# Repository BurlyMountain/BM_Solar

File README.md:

# BM_Solar 

This little PCB uses a Texas Instruments bq25185 chip to act as a solar charge controller and battery managment system for single cell Lithium Polymer, Lithium Ion, or Lithium Phosphate batteries.

It was designed specifically to work as a hat for Waveshare RP2040-LoRa boards to improve charging and battery managment as a solar meshtastic router/repeater. It is the same footprint and will solder directly on the backside of a RP2040-LoRa board.

*(Though it was designed for the RP2040-LoRa, it will work with any other board that can run off of a 4.5V input.)*

# Specifications

- 1A max charge rate (limited by solar input)
- Stable 4.5V output to a device
- 3-18V solar input voltage
- Automatically switches to battery power once solar drops below 3V
- Uses a 10kOhm thermistor to stop charging below 0F/32C in order to prevent damage to the battery
- Much more efficient than built in solar charging on most Meshtastic boards with near MPPT efficiency
- Selectable charge profile between LiPo/LiIon and LFP with an easy jumper
- built in voltage divider for battery voltage monitoring

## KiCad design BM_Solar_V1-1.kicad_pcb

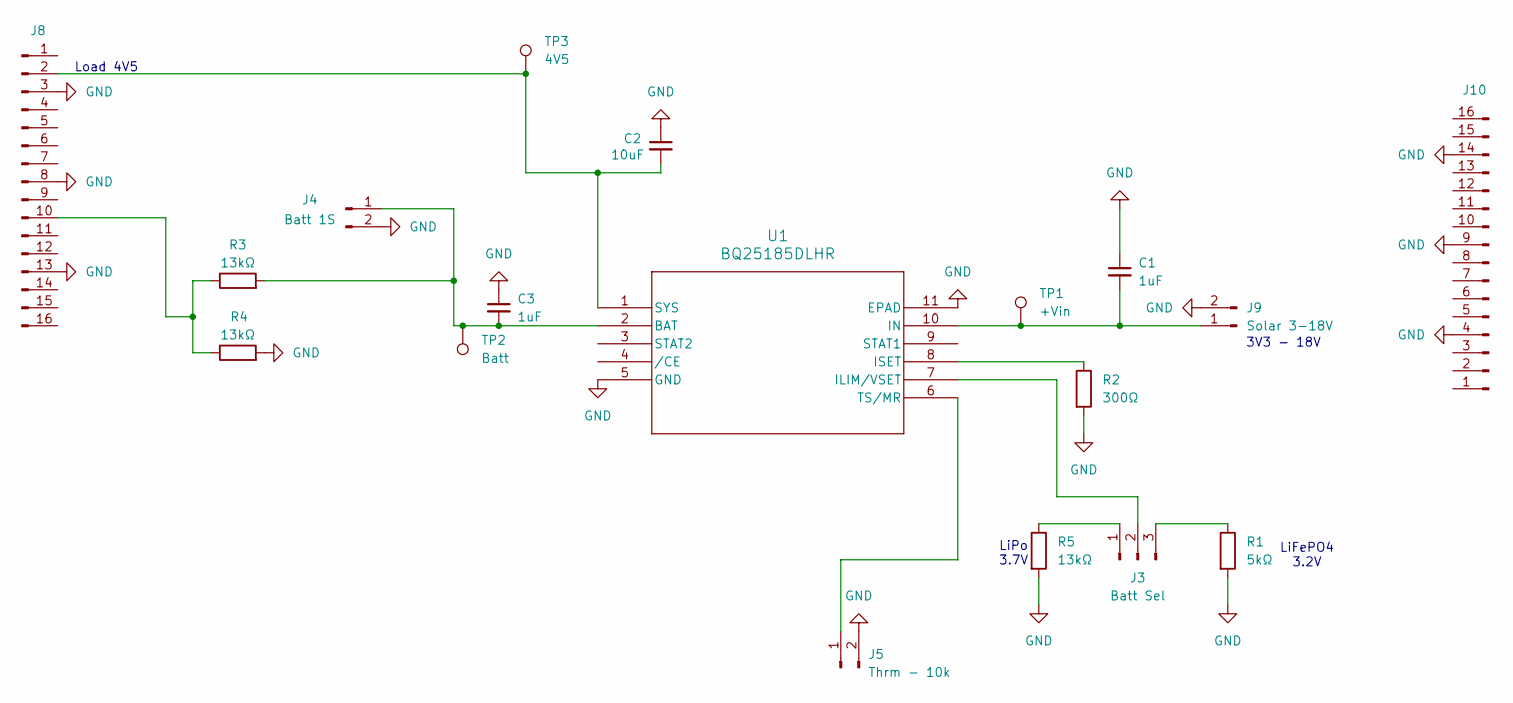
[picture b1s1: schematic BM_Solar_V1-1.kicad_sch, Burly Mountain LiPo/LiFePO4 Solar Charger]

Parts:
C1, C3: 1uF; C_0805_2012Metric
C2: 10uF; C_0805_2012Metric
J3: Batt Sel; PinHeader_1x03_P2.54mm_Vertical
J4: Batt 1S; JST_PH_S2B-PH-K_1x02_P2.00mm_Horizontal
J5: Thrm - 10k; SolderWire-0.5sqmm_1x02_P4.6mm_D0.9mm_OD2.1mm
J8, J10: Conn_01x16_Pin; PinHeader_1x16_P2.54mm_Vertical
J9: Solar 3-18V; JST_PH_S2B-PH-K_1x02_P2.00mm_Horizontal
R1: 5kΩ; R_0805_2012Metric
R2: 300Ω; R_0805_2012Metric
R3, R4, R5: 13kΩ; R_0805_2012Metric
TP1: +Vin; TestPoint_Pad_D1.0mm
TP2: Batt; TestPoint_Pad_D1.0mm
TP3: 4V5; TestPoint_Pad_D1.0mm
U1: BQ25185DLHR; WSON10_DLH_TEX

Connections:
GND: C1.1, C2.1, C3.1, J4.2, J5.2, J8.3, J8.8, J8.13, J9.2, J10.4, J10.9, J10.14, R1.2, R2.2, R4.2, R5.2, U1.5 (GND), U1.11 (EPAD)
unnamed: J3.1, R5.1
unnamed: J3.2, U1.7 (ILIM/VSET)
unnamed: J3.3, R1.1
unnamed: C3.2, J4.1, R3.2, TP2.1, U1.2 (BAT)
unnamed: J5.1, U1.6 (TS/MR)
unnamed: C2.2, J8.2, TP3.1, U1.1 (SYS)
unnamed: J8.10, R3.1, R4.1
unnamed: C1.2, J9.1, TP1.1, U1.10 (IN)
unnamed: R2.1, U1.8 (ISET)

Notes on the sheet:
Load 4V5
3V3 - 18V
LiFePO4 3.2V
LiPo 3.7V

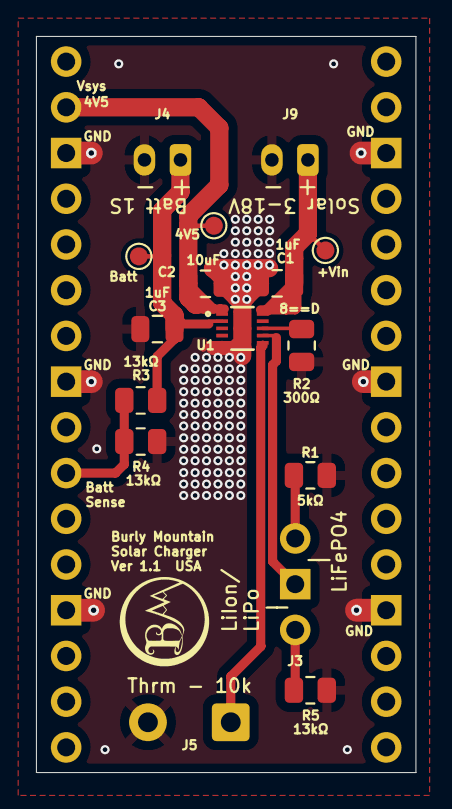
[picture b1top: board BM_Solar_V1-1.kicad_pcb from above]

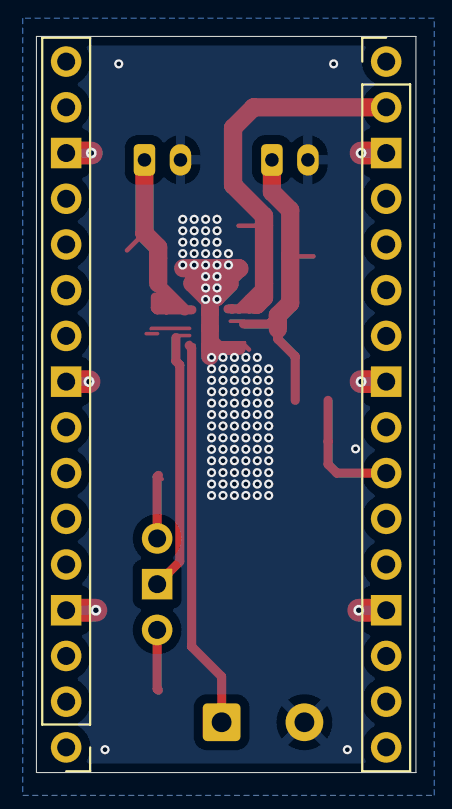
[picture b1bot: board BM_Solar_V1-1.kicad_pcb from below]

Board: 2 copper layers, 21.1 x 40.9 mm, 18 parts (2 on the bottom side), 10 nets.

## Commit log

2024-12-30 First commit - V1.1 board
2024-12-30 Changed name from bq25185-solar-lifep04 to BM_Solar_V1-1
2024-12-30 Deleted fp cache file
2024-12-30 Removed unneeded files
2024-12-30 Updated .gitignore
2024-12-30 Create README.md
    Initial README.md file created
2025-01-11 Changed to a 1x3 pin header for battery select, rearranged batt sense circuit, improved traces, and added more vias for more thermal dissipation.
